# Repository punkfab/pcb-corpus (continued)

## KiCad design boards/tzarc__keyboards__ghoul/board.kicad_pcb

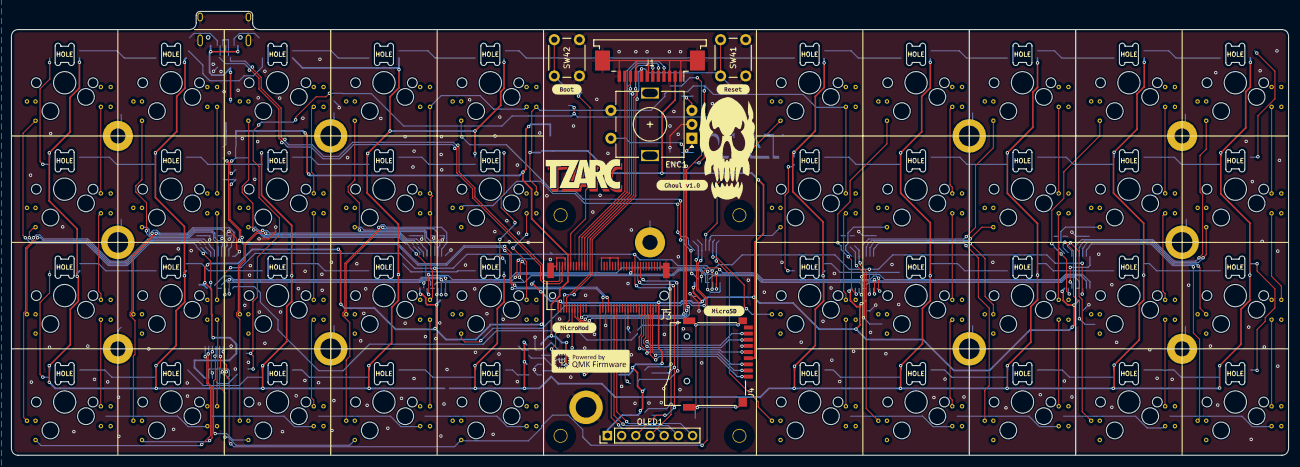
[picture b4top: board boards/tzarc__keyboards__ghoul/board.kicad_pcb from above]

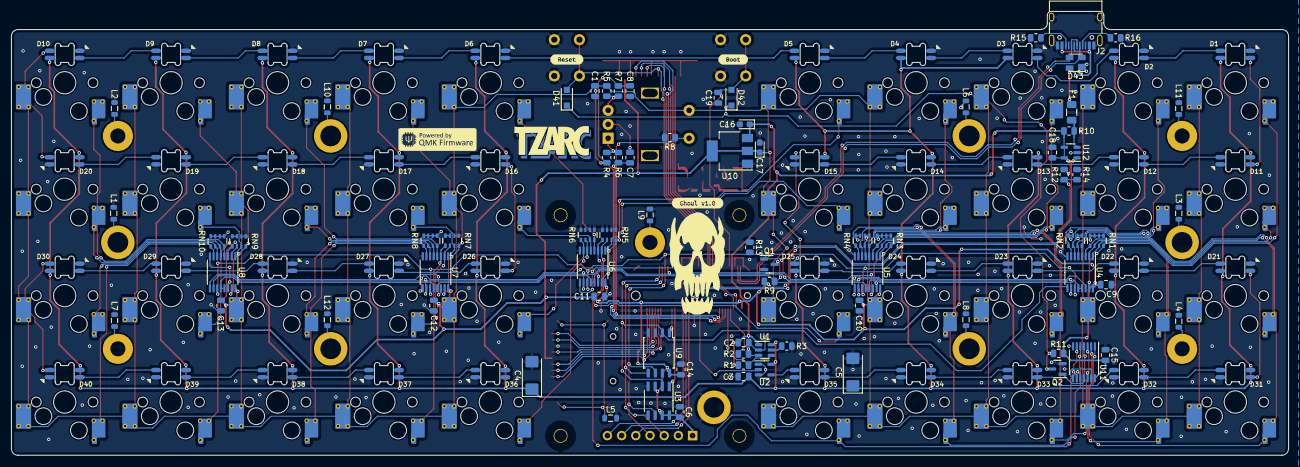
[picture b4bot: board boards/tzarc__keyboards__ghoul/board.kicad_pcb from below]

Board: 2 copper layers, 228.6 x 79.4 mm, 185 parts (88 on the bottom side), 148 nets.

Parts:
C1, C2, C3, C6, C7, C8, C9, C10, C11, C12, C13, C14, C15, C18, C19: 100n; C_0805_2012Metric
C4, C5: 100u; CP_EIA-6032-15_Kemet-U
C16, C17: 1u; CP_EIA-2012-15_AVX-P
D1, D2, D3, D4, D5, D6, D7, D8, D9, D10, D11, D12, D13, D14, D15, D16, D17, D18, D19, D20, D21, D22, D23, D24, D25, D26, D27, D28, D29, D30, D31, D32, D33, D34, D35, D36, D37, D38, D39, D40: SK6803; SK6803Mini-E
D41, D42: 1N4148WL; D_SOD-123F
D43: PRTR5V0U2X; SOT-143
ENC1: EC11N; RotaryEncoder_Alps_EC11E-Switch_Vertical_H20mm_Centred
F1: RF1989-000; Fuse_1206_3216Metric
H1, H3, H5, H7, H9, H11: L=2.5mm M2 Standoff; MountingHole_3.7mm_Pad
H2, H4, H6, H8, H10: M2 Screw; MountingHole_2.7mm_M2.5_Pad
J1: X10B25L12T; TE_1-84953-2_1x12-1MP_P1.0mm_Horizontal
J2: HRO_TYPE-C-31-M-12; USB_C_Receptacle_HRO_TYPE-C-31-M-12
J3: MICROMOD_E-2222; MicroMod_M.2-CONNECTOR-E
J4: microSD_TF-115; microSD_XunPu_TF-115
L1, L2, L3, L4, L5, L6, L7, L8, L9, L10, L11, L12: MPZ2012S101AT000; L_0805_2012Metric
NT1, NT2, NT3: NetTie-2_SMD_Pad0.2mm
OLED1: MTF185-107SY1; OLED_SSD1351_1.5inch
Q1, Q2: 2N7002; SOT-23
R1, R2, R4, R5, R6, R7, R8, R9, R11, R13, R15, R16: 5.1k; R_0805_2012Metric
R3, R12, R14: 75k; R_0805_2012Metric
R10: 0.005R; R_0805_2012Metric
RN1, RN2, RN3, RN4, RN5, RN6, RN7, RN8, RN9, RN10: 4x10k; R_Array_Convex_4x0603
SW1, SW2, SW3, SW4, SW5, SW6, SW7, SW8, SW9, SW10, SW11, SW12, SW13, SW14, SW15, SW16, SW17, SW18, SW19, SW20, SW21, SW22, SW23, SW24, SW25, SW26, SW27, SW28, SW29, SW30, SW31, SW32, SW33, SW34, SW35, SW36, SW37, SW38, SW39, SW40: MX; MX-1U-Hotswap
SW41: nRST; SW_PUSH_6mm
SW42: nBOOT; SW_PUSH_6mm
U1: TPS2553DBVR; SOT-23-6
U2: SN74AHCT1G125DBVR; SOT-23-5
U3: MB85RS64PNF-G-JNERE1; SO-8_3.9x4.9mm_P1.27mm
U4, U5, U6, U7, U8: MC74HC589ADTR2G; TSSOP-16_4.4x5mm_P0.65mm
U9: W25Q64JVSSIQ; SOIC-8_5.23x5.23mm_P1.27mm
U10: AZ1117H-3.3TRE1; SOT-223-3_TabPin2
U11: MC74HC08ADTR2G; TSSOP-14_4.4x5mm_P0.65mm
U12: INA180A4IDBVT; SOT-23-5
kibuzzard-62354CEE, kibuzzard-62354CEE#2: G***; kibuzzard-62354CEE
kibuzzard-62367B4C: G***; kibuzzard-62367B4C
kibuzzard-62367B65: G***; kibuzzard-62367B65
kibuzzard-62367BDD: G***; kibuzzard-62367BDD
kibuzzard-62367C14: G***; kibuzzard-62367C14
kibuzzard-62367E91: G***; kibuzzard-62367E91
kibuzzard-6236804E: G***; kibuzzard-6236804E

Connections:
5V_Post: C2.1, C16.1, J3.9 (USB_VIN), NT3.2, R1.1, R10.1, U1.1 (IN), U10.3 (VI)
5V_Pre: F1.1, NT2.2, R10.2
+3V3: C6.1, C9.1, C10.1, C11.1, C12.1, C13.1, C14.1, C15.1, C17.1, J1.2, J3.2 (3.3V), J3.74 (3.3V), J4.4 (VDD), NT1.2, OLED1.1 (VCC), R9.2, R11.2, U3.3 (~WP), U3.7 (~HOLD), U3.8 (VCC), U4.16 (VCC), U5.16 (VCC), U6.16 (VCC), U7.16 (VCC), U8.16 (VCC), U9.8 (VCC), U10.2 (VO), U11.14 (VCC)
/Matrix_1_2: U4.14 (SA/SerialIn), U5.9 (QH/SerialOut/MISO)
/Matrix_2_3: U5.14 (SA/SerialIn), U6.9 (QH/SerialOut/MISO)
/Matrix_3_4: U6.14 (SA/SerialIn), U7.9 (QH/SerialOut/MISO)
/Matrix_4_5: U7.14 (SA/SerialIn), U8.9 (QH/SerialOut/MISO)
/Matrix_Latch: Q1.3 (D), R9.1, U4.12 (Latch), U4.13 (SS/~PL), U5.12 (Latch), U5.13 (SS/~PL), U6.12 (Latch), U6.13 (SS/~PL), U7.12 (Latch), U7.13 (SS/~PL), U8.12 (Latch), U8.13 (SS/~PL)
CC1: J2.A5 (CC1), R16.2
CC2: J2.B5 (CC2), R15.2
CURR_LIM: R3.1, U1.5 (ILIM)
CURR_MEAS: J3.34 (A0), U12.1
D+: D43.3 (I/O2), J2.A6 (D+), J2.B6 (D+), J3.3 (USB_D+)
D-: D43.2 (I/O1), J2.A7 (D-), J2.B7 (D-), J3.5 (USB_D-)
DBG_RX_TGT_TX: J1.11, J3.17 (TX1)
DBG_TX_TGT_RX: J1.10, J3.19 (RX1)
EEPROM_CS: J3.50 (AUD_BCLK), U3.1 (~CS)
ENC_A: C7.1, J3.16 (I2C_~INT), R6.1
ENC_B: C8.1, J3.14 (I2C_SCL), R7.1
ENC_SW: ENC1.S2, J3.18 (D1/CAM_TRIG), R8.1
FLASH_CS: J3.52 (AUD_LRCLK), U9.1 (~CS)
GND: C1.2, C2.2, C3.2, C4.2, C5.2, C6.2, C7.2, C8.2, C9.2, C10.2, C11.2, C12.2, C13.2, C14.2, C15.2, C16.2, C17.2, C18.2, C19.2, D1.1 (VSS), D2.1 (VSS), D3.1 (VSS), D4.1 (VSS), D5.1 (VSS), D6.1 (VSS), D7.1 (VSS), D8.1 (VSS), D9.1 (VSS), D10.1 (VSS), D11.1 (VSS), D12.1 (VSS), D13.1 (VSS), D14.1 (VSS), D15.1 (VSS), D16.1 (VSS), D17.1 (VSS), D18.1 (VSS), D19.1 (VSS), D20.1 (VSS), D21.1 (VSS), D22.1 (VSS), D23.1 (VSS), D24.1 (VSS), D25.1 (VSS), D26.1 (VSS), D27.1 (VSS), D28.1 (VSS), D29.1 (VSS), D30.1 (VSS), D31.1 (VSS), D32.1 (VSS), D33.1 (VSS), D34.1 (VSS), D35.1 (VSS), D36.1 (VSS), D37.1 (VSS), D38.1 (VSS), D39.1 (VSS), D40.1 (VSS), D43.1 (GND), ENC1.C, J1.1, J1.3, J1.7, J1.9, J1.12, J1.MP (MountPin), J2.A1 (GND), J2.A12 (GND), J2.B1 (GND), J2.B12 (GND), J2.S1 (SHIELD), J3.1 (GND), J3.7 (GND), J3.33 (GND), J3.36 (GND), J3.39 (GND), J3.45 (GND), J3.75 (GND), J3.M (Mountpoint), J3.S (Screw), J4.6 (VSS), L1.2, L2.2, L3.2, L4.2, L5.2, L6.2, L7.2, L8.2, L9.2, L10.2, L11.2, L12.2, OLED1.2 (GND), Q1.2 (S), Q2.2 (S), R2.2, R3.2, R8.2, R13.1, R14.1, R15.1, R16.1, RN1.1 (R1.1), RN1.2 (R2.1), RN1.3 (R3.1), RN1.4 (R4.1), RN2.5 (R4.2), RN2.6 (R3.2), RN2.7 (R2.2), RN2.8 (R1.2), RN3.1 (R1.1), RN3.2 (R2.1), RN3.3 (R3.1), RN3.4 (R4.1), RN4.5 (R4.2), RN4.6 (R3.2), RN4.7 (R2.2), RN4.8 (R1.2), RN5.1 (R1.1), RN5.2 (R2.1), RN5.3 (R3.1), RN5.4 (R4.1), RN6.5 (R4.2), RN6.6 (R3.2), RN6.7 (R2.2), RN6.8 (R1.2), RN7.1 (R1.1), RN7.2 (R2.1), RN7.3 (R3.1), RN7.4 (R4.1), RN8.5 (R4.2), RN8.6 (R3.2), RN8.7 (R2.2), RN8.8 (R1.2), RN9.1 (R1.1), RN9.2 (R2.1), RN9.3 (R3.1), RN9.4 (R4.1), RN10.5 (R4.2), RN10.6 (R3.2), RN10.7 (R2.2), RN10.8 (R1.2), SW41.2, SW42.2, U1.2 (GND), U2.1, U2.3 (GND), U3.4 (GND), U4.8 (GND), U5.8 (GND), U6.8 (GND), U7.8 (GND), U8.8 (GND), U8.14 (SA/SerialIn), U9.4 (GND), U10.1 (GND), U11.7 (GND), U12.2 (GND)
Key_Pullup: C1.1, ENC1.S1, NT1.1, R4.1, R5.1, SW1.1, SW2.1, SW3.1, SW4.1, SW5.1, SW6.1, SW7.1, SW8.1, SW9.1, SW10.1, SW11.1, SW12.1, SW13.1, SW14.1, SW15.1, SW16.1, SW17.1, SW18.1, SW19.1, SW20.1, SW21.1, SW22.1, SW23.1, SW24.1, SW25.1, SW26.1, SW27.1, SW28.1, SW29.1, SW30.1, SW31.1, SW32.1, SW33.1, SW34.1, SW35.1, SW36.1, SW37.1, SW38.1, SW39.1, SW40.1
MATRIX_CS: J3.55 (SPI_~CS), Q1.1 (G), U4.10 (OutputEnable/~CS), U5.10 (OutputEnable/~CS), U6.10 (OutputEnable/~CS), U7.10 (OutputEnable/~CS), U8.10 (OutputEnable/~CS)
MISO: J3.61 (SPI_MISO), U3.2 (MISO), U4.9 (QH/SerialOut/MISO), U9.2 (DO(IO1))
MOSI: J3.59 (SPI_MOSI), OLED1.3 (MOSI), U3.5 (MOSI), U9.5 (DI(IO0))
unnamed: C18.1, NT3.1, R12.2, U12.4 (-), U12.5 (V+)
unnamed: D1.2 (DIN), D11.4 (DOUT)
unnamed: D1.4 (DOUT), D2.2 (DIN)
unnamed: D2.4 (DOUT), D3.2 (DIN)
unnamed: D3.4 (DOUT), D4.2 (DIN)
unnamed: D4.4 (DOUT), D5.2 (DIN)
unnamed: D5.4 (DOUT), D6.2 (DIN)
unnamed: D6.4 (DOUT), D7.2 (DIN)
unnamed: D7.4 (DOUT), D8.2 (DIN)
unnamed: D8.4 (DOUT), D9.2 (DIN)
unnamed: D9.4 (DOUT), D10.2 (DIN)
unnamed: D10.4 (DOUT), D20.2 (DIN)
unnamed: D11.2 (DIN), D12.4 (DOUT)
unnamed: D12.2 (DIN), D13.4 (DOUT)
unnamed: D13.2 (DIN), D14.4 (DOUT)
unnamed: D14.2 (DIN), D15.4 (DOUT)
unnamed: D15.2 (DIN), D25.4 (DOUT)
unnamed: D16.2 (DIN), D17.4 (DOUT)
unnamed: D16.4 (DOUT), D26.2 (DIN)
unnamed: D17.2 (DIN), D18.4 (DOUT)
unnamed: D18.2 (DIN), D19.4 (DOUT)
unnamed: D19.2 (DIN), D20.4 (DOUT)
unnamed: D21.2 (DIN), D31.4 (DOUT)
unnamed: D21.4 (DOUT), D22.2 (DIN)
unnamed: D22.4 (DOUT), D23.2 (DIN)
unnamed: D23.4 (DOUT), D24.2 (DIN)
unnamed: D24.4 (DOUT), D25.2 (DIN)
unnamed: D26.4 (DOUT), D27.2 (DIN)
unnamed: D27.4 (DOUT), D28.2 (DIN)
unnamed: D28.4 (DOUT), D29.2 (DIN)
unnamed: D29.4 (DOUT), D30.2 (DIN)
unnamed: D30.4 (DOUT), D40.2 (DIN)
unnamed: D31.2 (DIN), D32.4 (DOUT)
unnamed: D32.2 (DIN), D33.4 (DOUT)
unnamed: D33.2 (DIN), D34.4 (DOUT)
unnamed: D34.2 (DIN), D35.4 (DOUT)
unnamed: D36.2 (DIN), D37.4 (DOUT)
unnamed: D37.2 (DIN), D38.4 (DOUT)
unnamed: D38.2 (DIN), D39.4 (DOUT)
unnamed: D39.2 (DIN), D40.4 (DOUT)
unnamed: D41.1 (K), D42.1 (K), Q2.3 (D), R11.1
unnamed: H1.1, L1.1
unnamed: H2.1, L2.1
unnamed: H3.1, L3.1
unnamed: H4.1, L4.1
unnamed: H5.1, L6.1
unnamed: H6.1, L7.1
unnamed: H7.1, L8.1
unnamed: H8.1, L9.1
unnamed: H9.1, L10.1
unnamed: H10.1, L11.1
unnamed: H11.1, L12.1
unnamed: J4.S (SHIELD), L5.1
unnamed: NT2.1, U12.3 (+)
unnamed: Q2.1 (G), U11.11 (4Y)
OLED_CS: J3.40 (G0/BUS0), OLED1.5 (~CS)
OLED_DC: J3.42 (G1/BUS1), OLED1.6 (D/C)
OLED_RST: J3.44 (G2/BUS2), OLED1.7 (RST)
ROT_A: ENC1.A, R4.2, R6.2
ROT_B: ENC1.B, R5.2, R7.2
SCK: J3.57 (SPI_SCK), OLED1.4 (SCK), R13.2, U3.6 (SCK), U4.11 (ShiftClock/SCK), U5.11 (ShiftClock/SCK), U6.11 (ShiftClock/SCK), U7.11 (ShiftClock/SCK), U8.11 (ShiftClock/SCK), U9.6 (CLK)
SDIO_CLK: J3.60 (SPI_SCK1/SDIO_CLK), J4.5 (CLK)
SDIO_CMD: J3.62 (SPI_MOSI1/SDIO_CMD), J4.3 (CMD)
SDIO_DATA0: J3.64 (SPI_MISO1/SDIO_DATA0), J4.7 (DAT0)
SDIO_DATA1: J3.66 (SDIO_DATA1), J4.8 (DAT1)
SDIO_DATA2: J3.68 (SDIO_DATA2), J4.1 (DAT2)
SDIO_DATA3: J3.70 (SPI_~CS1/SDIO_DATA3), J4.2 (DAT3/CD)
SK6803_DAT_3V3: J3.32 (PWM0), U2.2
SK6803_DAT_5V: D35.2 (DIN), U2.4
SK6803_EN: J3.10 (D0), R2.1, U1.3 (EN)
SK6803_NFAULT: J3.12 (I2C_SDA), R1.2, U1.4 (~FAULT)
SK6803_PWR: C3.1, C4.1, C5.1, D1.3 (VDD), D2.3 (VDD), D3.3 (VDD), D4.3 (VDD), D5.3 (VDD), D6.3 (VDD), D7.3 (VDD), D8.3 (VDD), D9.3 (VDD), D10.3 (VDD), D11.3 (VDD), D12.3 (VDD), D13.3 (VDD), D14.3 (VDD), D15.3 (VDD), D16.3 (VDD), D17.3 (VDD), D18.3 (VDD), D19.3 (VDD), D20.3 (VDD), D21.3 (VDD), D22.3 (VDD), D23.3 (VDD), D24.3 (VDD), D25.3 (VDD), D26.3 (VDD), D27.3 (VDD), D28.3 (VDD), D29.3 (VDD), D30.3 (VDD), D31.3 (VDD), D32.3 (VDD), D33.3 (VDD), D34.3 (VDD), D35.3 (VDD), D36.3 (VDD), D37.3 (VDD), D38.3 (VDD), D39.3 (VDD), D40.3 (VDD), U1.6 (OUT), U2.5 (VCC)
SWCLK: J1.5, J3.21 (SWDCK)
SWDIO: J1.4, J3.23 (SWDIO)
SWO: J1.6, J3.8 (G11/SWO)
VBUS: D43.4 (VCC), F1.2, J2.A4 (VBUS), J2.A9 (VBUS), J2.B4 (VBUS), J2.B9 (VBUS)
VOLT_MEAS: J3.38 (A1), R12.1, R14.2
k00: RN1.8 (R1.2), SW1.2, U4.15 (A)
k01: RN1.7 (R2.2), SW11.2, U4.1 (B)
k02: RN1.6 (R3.2), SW21.2, U4.2 (C)
k03: RN1.5 (R4.2), SW31.2, U4.3 (D), U11.1 (1A)
k03&&k07: U11.3 (1Y), U11.12 (4A)
k04: RN2.4 (R4.1), SW2.2, U4.4 (E)
k05: RN2.3 (R3.1), SW12.2, U4.5 (F)
k06: RN2.2 (R2.1), SW22.2, U4.6 (G)
k07: RN2.1 (R1.1), SW32.2, U4.7 (H), U11.2 (1B)
k10: RN3.8 (R1.2), SW3.2, U5.15 (A)
k11: RN3.7 (R2.2), SW13.2, U5.1 (B)
k12: RN3.6 (R3.2), SW23.2, U5.2 (C)
k13: RN3.5 (R4.2), SW33.2, U5.3 (D), U11.4 (2A)
k13&&k17: U11.6 (2Y), U11.9 (3A)
k13&&k17&&k23: U11.8 (3Y), U11.13 (4B)
k14: RN4.4 (R4.1), SW4.2, U5.4 (E)
k15: RN4.3 (R3.1), SW14.2, U5.5 (F)
k16: RN4.2 (R2.1), SW24.2, U5.6 (G)
k17: RN4.1 (R1.1), SW34.2, U5.7 (H), U11.5 (2B)
k20: RN5.8 (R1.2), SW5.2, U6.15 (A)
k21: RN5.7 (R2.2), SW15.2, U6.1 (B)
k22: RN5.6 (R3.2), SW25.2, U6.2 (C)
k23: RN5.5 (R4.2), SW35.2, U6.3 (D), U11.10 (3B)
k24: RN6.4 (R4.1), SW6.2, U6.4 (E)
k25: RN6.3 (R3.1), SW16.2, U6.5 (F)
k26: RN6.2 (R2.1), SW26.2, U6.6 (G)
k27: RN6.1 (R1.1), SW36.2, U6.7 (H)
k30: RN7.8 (R1.2), SW7.2, U7.15 (A)
k31: RN7.7 (R2.2), SW17.2, U7.1 (B)
k32: RN7.6 (R3.2), SW27.2, U7.2 (C)
k33: RN7.5 (R4.2), SW37.2, U7.3 (D)
k34: RN8.4 (R4.1), SW8.2, U7.4 (E)
k35: RN8.3 (R3.1), SW18.2, U7.5 (F)
k36: RN8.2 (R2.1), SW28.2, U7.6 (G)
k37: RN8.1 (R1.1), SW38.2, U7.7 (H)
k40: RN9.8 (R1.2), SW9.2, U8.15 (A)
k41: RN9.7 (R2.2), SW19.2, U8.1 (B)
k42: RN9.6 (R3.2), SW29.2, U8.2 (C)
k43: RN9.5 (R4.2), SW39.2, U8.3 (D)
k44: RN10.4 (R4.1), SW10.2, U8.4 (E)
k45: RN10.3 (R3.1), SW20.2, U8.5 (F)
k46: RN10.2 (R2.1), SW30.2, U8.6 (G)
k47: RN10.1 (R1.1), SW40.2, U8.7 (H)
nBOOT: C19.1, D42.2 (A), J3.11 (~BOOT!), SW42.1
nRESET: D41.2 (A), J1.8, J3.6 (~RESET!), SW41.1

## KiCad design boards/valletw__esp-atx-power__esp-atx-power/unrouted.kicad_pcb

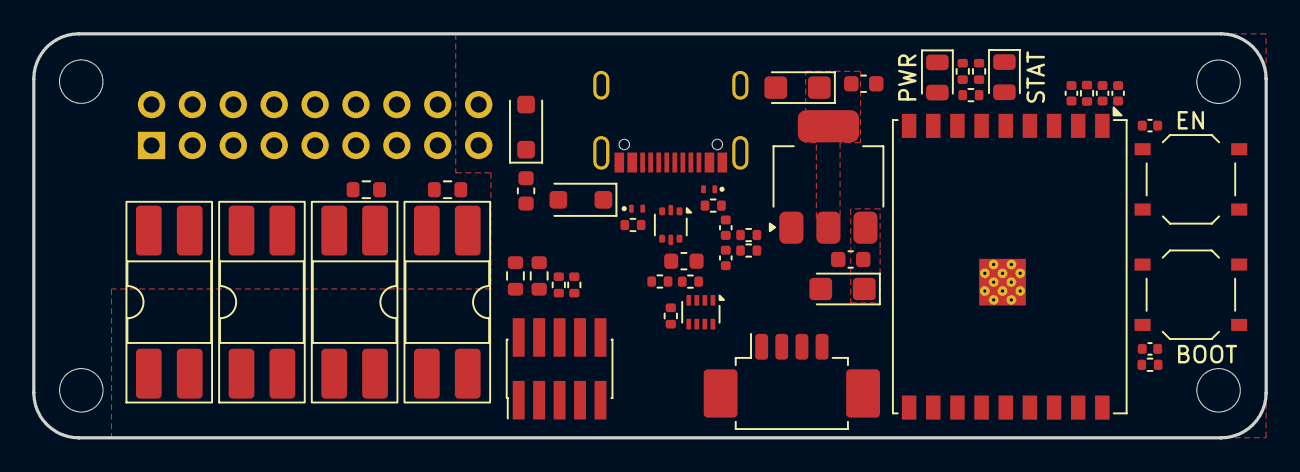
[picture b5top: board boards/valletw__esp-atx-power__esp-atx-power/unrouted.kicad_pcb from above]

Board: 4 copper layers, 76.6 x 25.1 mm, 55 parts (0 on the bottom side), 45 nets, no tracks yet.

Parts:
C101, C105, C106: 100n; C_0402_1005Metric
C102: 10u; C_0402_1005Metric
C103, C110: 100n; C_0603_1608Metric
C104, C111: 10u; CP_EIA-3216-18_Kemet-A
C107: 1u; C_0402_1005Metric
C108, C109: C_0402_1005Metric
D101, D102: TPD1E05U06; Texas_DPY0002A_0.6x1mm_P0.65mm
D103: Red; LED_0805_2012Metric
D104: Green; LED_0805_2012Metric
D105, D106: SMF5.0A; D_SOD-123F
J101: Conn_ARM_JTAG_SWD_10; PinHeader_2x05_P1.27mm_Vertical_SMD
J102: Conn_02x09_Odd_Even; PinHeader_2x09_P2.54mm_Horizontal
J103: Conn_01x04; Molex_PicoBlade_53261-0471_1x04-1MP_P1.25mm_Horizontal
J105: GT-USB-7010ASV; USB_C_Receptacle_G-Switch_GT-USB-7010ASV
K101, K102, K103, K104: G3VM-61D1; DIP-4_W8.89mm_SMDSocket_LongPads
L101, L102: Ferrite Bead; L_0603_1608Metric
MH101, MH102, MH103, MH104: MountingHole_2.7mm_M2.5_ISO7380
R101, R102, R104, R106: 390; R_0603_1608Metric
R103, R108, R109, R117, R118: 10k; R_0402_1005Metric
R105, R107: 4.7k; R_0402_1005Metric
R110, R111: 5.1k; R_0402_1005Metric
R112, R113: 22; R_0402_1005Metric
R114, R115: 680; R_0402_1005Metric
R116: 0; R_0402_1005Metric
SW101, SW102: TS-1187A-B-A-B; SW_Push_1P1T_XKB_TS-1187A
U101: ESP32-C3-WROOM-02U
U102: AMS1117-3.3; SOT-223-3_TabPin2
U103: USBLC6-2P6; SOT-666
U104: TPS2116DRL; SOT-583-8

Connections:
+3V3: C101.2, C102.1, C104.1, C110.1, D103.2 (A), J101.1 (VTref), J103.1, K103.4 (D2), K104.4 (D2), R103.2, R108.2, R109.2, U101.1 (3V3), U102.2 (VO)
+5V: C103.1, C111.1, U102.3 (VI), U104.2 (VOUT), U104.7 (VOUT)
+5VA: D105.1 (A1), J102.17, L102.1
/BOOT: C106.1, SW102.1, U101.8 (IO9)
/EN: C105.1, C107.1, J101.10 (~RESET), R103.1, SW101.1, U101.2 (EN)
/HDD_LED: K104.3 (D1), R107.2, U101.10 (IO10)
/HDD_LED_N: J102.13, J102.14, K104.2 (K)
/HDD_LED_P: J102.15, J102.16, R106.2
/PWR_LED: K103.3 (D1), R105.2, U101.15 (IO3)
/PWR_LED_N: J102.9, J102.10, K103.2 (K)
/PWR_LED_P: J102.11, J102.12, R104.2
/PWR_SW: K101.1 (A), U101.18 (IO0)
/PWR_SW_N: J102.3, J102.4, K101.3 (D1)
/PWR_SW_P: J102.1, J102.2, K101.4 (D2)
/RST_SW: K102.1 (A), U101.17 (IO1)
/RST_SW_N: J102.7, J102.8, K102.3 (D1)
/RST_SW_P: J102.5, J102.6, K102.4 (D2)
/RX: J103.3, U101.11 (IO20/RXD)
/STATUS: D104.2 (A), R109.1, U101.7 (IO8)
/TCK: J101.4 (SWCLK/TCK), U101.5 (IO6)
/TDI: J101.8 (NC/TDI), U101.4 (IO5)
/TDO: J101.6 (SWO/TDO), U101.6 (IO7)
/TMS: J101.2 (SWDIO/TMS), U101.3 (IO4)
/TX: J103.2, U101.12 (IO21/TXD)
/USB_DN: C108.1, R112.1, U103.6 (I/O1)
/USB_DP: C109.1, R113.1, U103.4 (I/O2)
/USB_EDN: R112.2, U101.13 (IO18)
/USB_EDP: R113.2, U101.14 (IO19)
/USB_IN_CC1: D101.2 (A2), J105.A5 (CC1), R110.2
/USB_IN_CC2: D102.2 (A2), J105.B5 (CC2), R111.2
/USB_IN_DN: J105.A7 (D-), J105.B7 (D-), U103.1 (I/O1)
/USB_IN_DP: J105.A6 (D+), J105.B6 (D+), U103.3 (I/O2)
GND: C101.1, C102.2, C103.2, C104.2, C105.2, C106.2, C107.2, C108.2, C109.2, C110.2, C111.2, D101.1 (A1), D102.1 (A1), D105.2 (A2), D106.2 (A2), J101.3 (GND), J101.5 (GND), J101.9 (GNDDetect), J102.18, J103.4, J105.A1 (GND), J105.A12 (GND), J105.B1 (GND), J105.B12 (GND), J105.S1 (SHIELD), R101.1, R102.1, R105.1, R107.1, R110.1, R111.1, R114.1, R115.1, R118.2, SW101.2, SW102.2, U101.9 (GND), U101.19 (GND), U102.1 (GND), U103.2 (GND), U104.1 (GND)
unnamed: D103.1 (K), R114.2
unnamed: D104.1 (K), R115.2
unnamed: K101.2 (K), R101.2
unnamed: K102.2 (K), R102.2
unnamed: K103.1 (A), R104.1
unnamed: K104.1 (A), R106.1
unnamed: R108.1, U101.16 (IO2)
unnamed: R116.2, U104.5 (MODE)
unnamed: R117.1, R118.1, U104.4 (PR1)
unnamed: L101.2, R116.1, R117.2, U104.3 (VIN1)
unnamed: L102.2, U104.6 (VIN2)
VBUS: D106.1 (A1), J105.A4 (VBUS), J105.A9 (VBUS), J105.B4 (VBUS), J105.B9 (VBUS), L101.1, U103.5 (VBUS)
